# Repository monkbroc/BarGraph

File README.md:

# BarGraph

Carrier board for 3 Adafruit [bar graph LED displays](https://www.adafruit.com/product/1921)

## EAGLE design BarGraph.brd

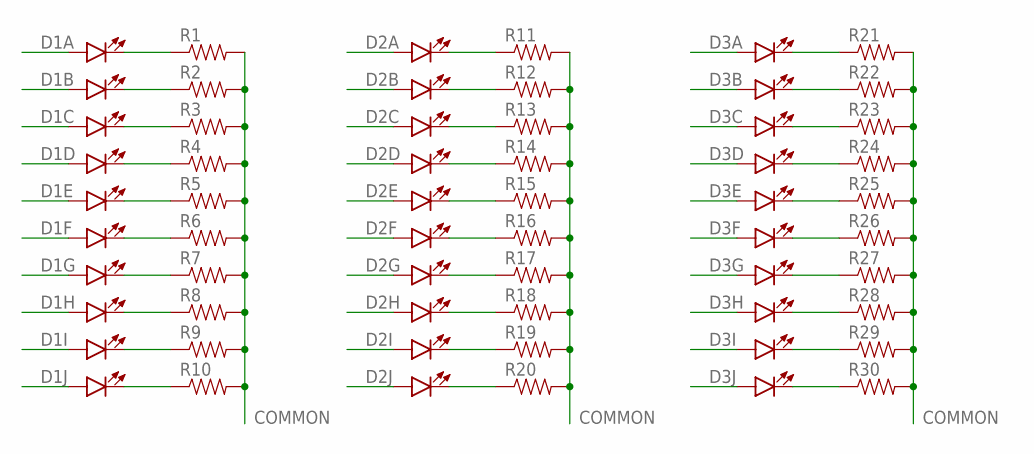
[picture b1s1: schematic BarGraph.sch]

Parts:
D1, D2, D3: LED_BARGRAPH_10; LED_BARGAPH_10
R1, R2, R3, R4, R5, R6, R7, R8, R9, R10, R11, R12, R13, R14, R15, R16, R17, R18, R19, R20, R21, R22, R23, R24, R25, R26, R27, R28, R29, R30: RESISTORPTH-1/4W; AXIAL-0.4

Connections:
COMMON: R1.P$2 (2), R2.P$2 (2), R3.P$2 (2), R4.P$2 (2), R5.P$2 (2), R6.P$2 (2), R7.P$2 (2), R8.P$2 (2), R9.P$2 (2), R10.P$2 (2), R11.P$2 (2), R12.P$2 (2), R13.P$2 (2), R14.P$2 (2), R15.P$2 (2), R16.P$2 (2), R17.P$2 (2), R18.P$2 (2), R19.P$2 (2), R20.P$2 (2), R21.P$2 (2), R22.P$2 (2), R23.P$2 (2), R24.P$2 (2), R25.P$2 (2), R26.P$2 (2), R27.P$2 (2), R28.P$2 (2), R29.P$2 (2), R30.P$2 (2)
unnamed: D1.20 (C), R1.P$1 (1)
unnamed: D1.19 (C), R2.P$1 (1)
unnamed: D1.18 (C), R3.P$1 (1)
unnamed: D1.17 (C), R4.P$1 (1)
unnamed: D1.16 (C), R5.P$1 (1)
unnamed: D1.15 (C), R6.P$1 (1)
unnamed: D1.14 (C), R7.P$1 (1)
unnamed: D1.13 (C), R8.P$1 (1)
unnamed: D1.12 (C), R9.P$1 (1)
unnamed: D1.11 (C), R10.P$1 (1)
unnamed: D2.20 (C), R11.P$1 (1)
unnamed: D2.19 (C), R12.P$1 (1)
unnamed: D2.18 (C), R13.P$1 (1)
unnamed: D2.17 (C), R14.P$1 (1)
unnamed: D2.16 (C), R15.P$1 (1)
unnamed: D2.15 (C), R16.P$1 (1)
unnamed: D2.14 (C), R17.P$1 (1)
unnamed: D2.13 (C), R18.P$1 (1)
unnamed: D2.12 (C), R19.P$1 (1)
unnamed: D2.11 (C), R20.P$1 (1)
unnamed: D3.20 (C), R21.P$1 (1)
unnamed: D3.19 (C), R22.P$1 (1)
unnamed: D3.18 (C), R23.P$1 (1)
unnamed: D3.17 (C), R24.P$1 (1)
unnamed: D3.16 (C), R25.P$1 (1)
unnamed: D3.15 (C), R26.P$1 (1)
unnamed: D3.14 (C), R27.P$1 (1)
unnamed: D3.13 (C), R28.P$1 (1)
unnamed: D3.12 (C), R29.P$1 (1)
unnamed: D3.11 (C), R30.P$1 (1)

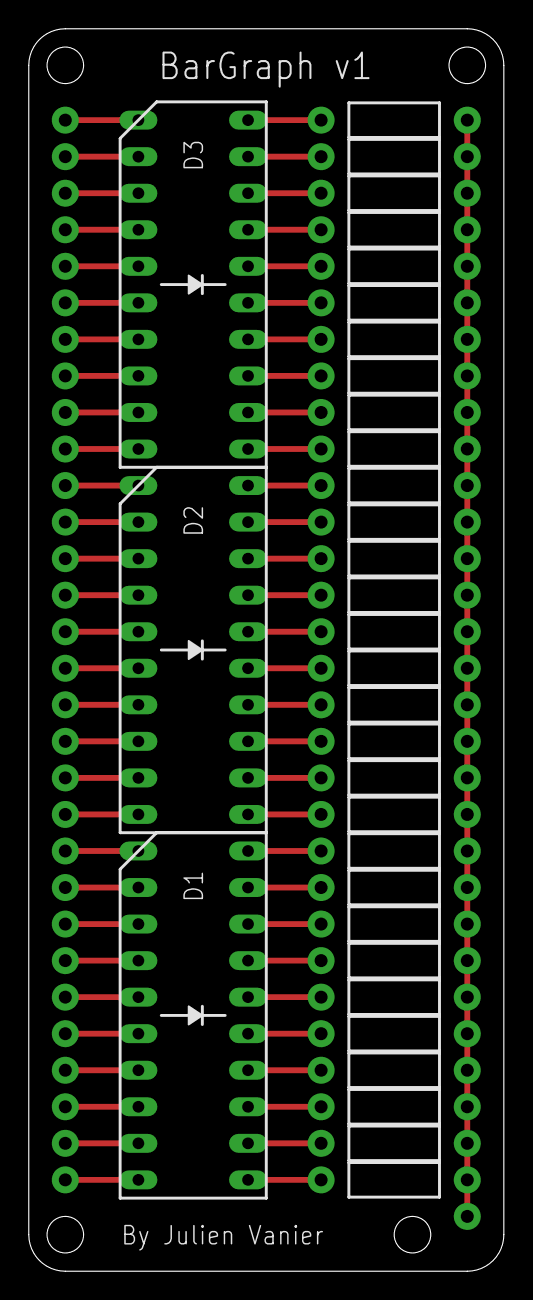
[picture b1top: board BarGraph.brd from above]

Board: 2 copper layers, 33.0 x 86.4 mm, 33 parts (0 on the bottom side), 31 nets.

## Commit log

2018-10-08 V1 made at OSH Park

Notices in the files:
parts and their libraries:
SparkFun-LED: Licensing: Creative Commons ShareAlike 4.0 International - https://creativecommons.org/licenses/by-sa/4.0
